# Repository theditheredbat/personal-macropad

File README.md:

# My Macropad
Good Morning! I created a macropad made to be  
used for video editing with the help of  
HackClub's infamous Hackpad tutorial.  

## Firmware
Made with KMK.  
Knob: scrub the timeline  
Right button: Go to In point  
Left button: Go to Out point  
Up button: Clear In and Out  
Down button: Save
## PCB
Made in KiCAD  
Schematic:  

PCB:  

## CAD
Made in Fusion360  
Bottom:  
  
Top:  

## BOM
1x XIAO RP2040  
1x EC11 Rotary Encoder  
4x Cherry MX Switches  
4x DSA Keycaps  
4x M3x16 Bolt  
4x M3 Heatset  
1x PCB  
1x 3D Printed Case

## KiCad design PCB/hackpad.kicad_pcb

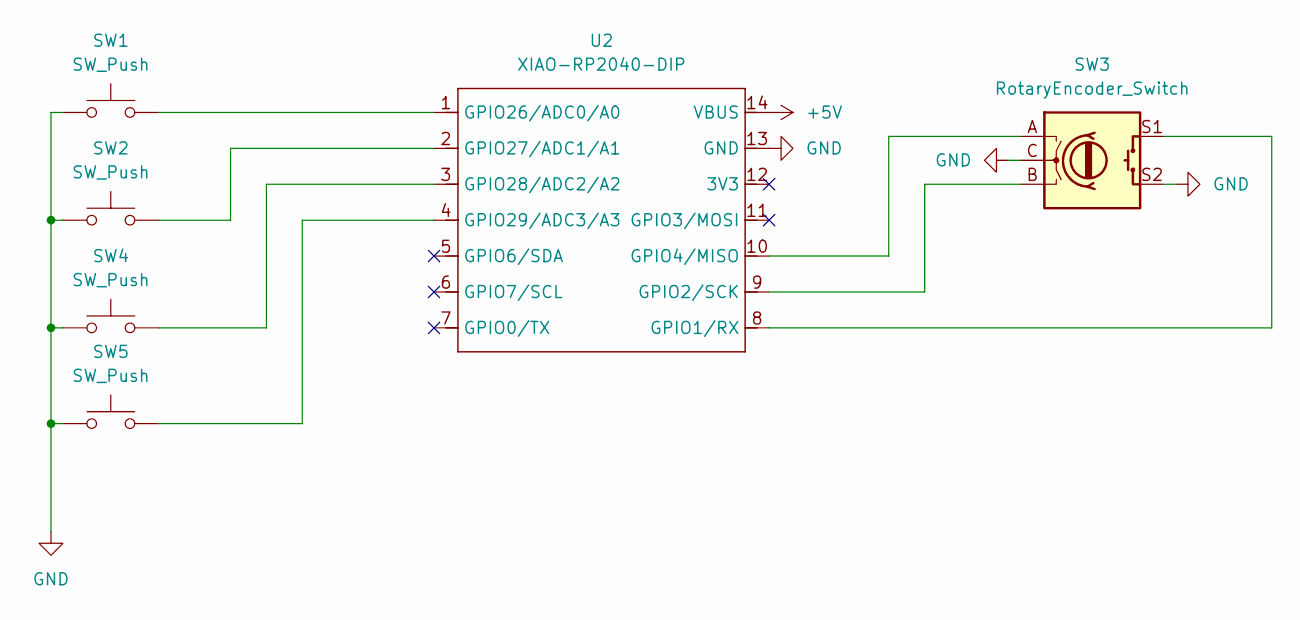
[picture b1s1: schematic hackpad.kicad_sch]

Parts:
SW1, SW2, SW4, SW5: SW_Push; SW_Cherry_MX_1.00u_PCB
SW3: RotaryEncoder_Switch; RotaryEncoder_Alps_EC11E-Switch_Vertical_H20mm_CircularMoun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
U2: XIAO-RP2040-DIP

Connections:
+5V: U2.14 (VBUS)
GND: SW1.1, SW2.1, SW3.C, SW3.S2, SW4.1, SW5.1, U2.13 (GND)
unnamed: SW3.S1, U2.8 (GPIO1/RX)
unnamed: SW3.B, U2.9 (GPIO2/SCK)
unnamed: SW3.A, U2.10 (GPIO4/MISO)
unnamed: SW1.2, U2.1 (GPIO26/ADC0/A0)
unnamed: SW2.2, U2.2 (GPIO27/ADC1/A1)
unnamed: SW4.2, U2.3 (GPIO28/ADC2/A2)
unnamed: SW5.2, U2.4 (GPIO29/ADC3/A3)

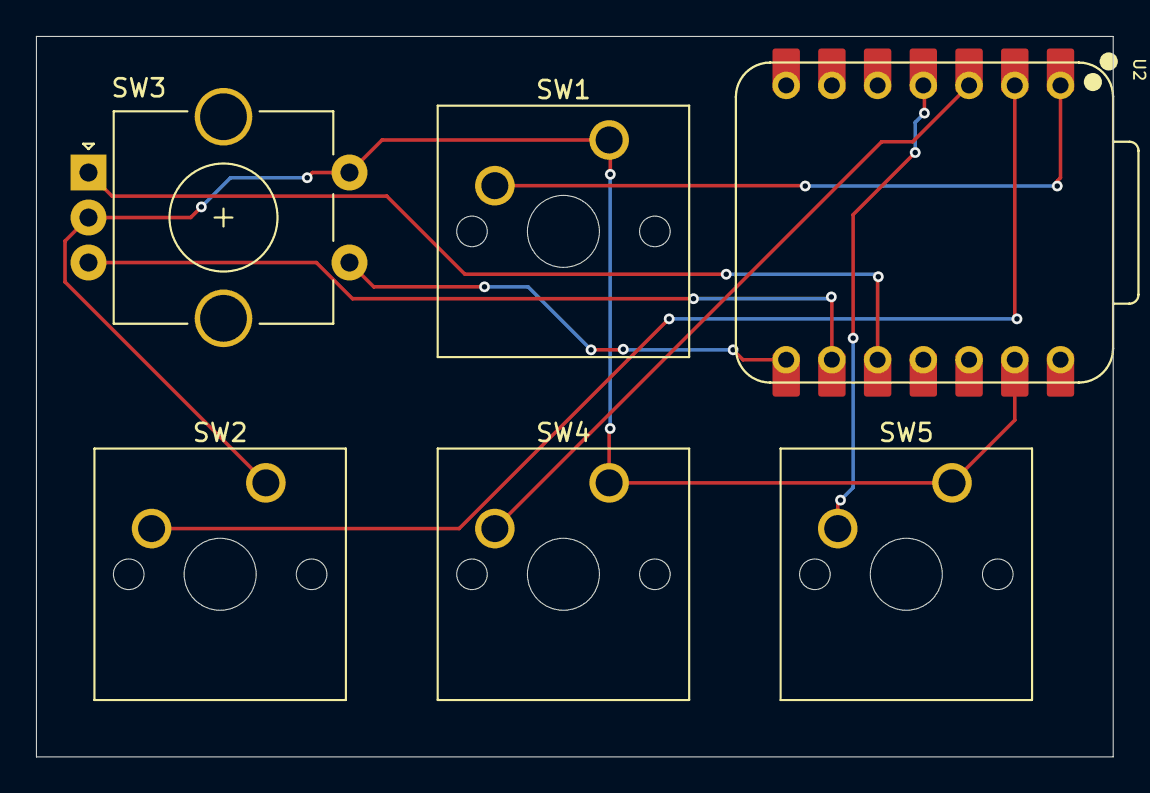
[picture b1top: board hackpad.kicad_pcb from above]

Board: 2 copper layers, 59.8 x 40.0 mm, 6 parts (0 on the bottom side), 8 nets.

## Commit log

2025-11-30 Line Breaks in README
2025-11-30 Changed README formatting
2025-11-30 README linebreaks
2025-11-30 Switched to Markdown
2025-11-30 Fixed README formatting
